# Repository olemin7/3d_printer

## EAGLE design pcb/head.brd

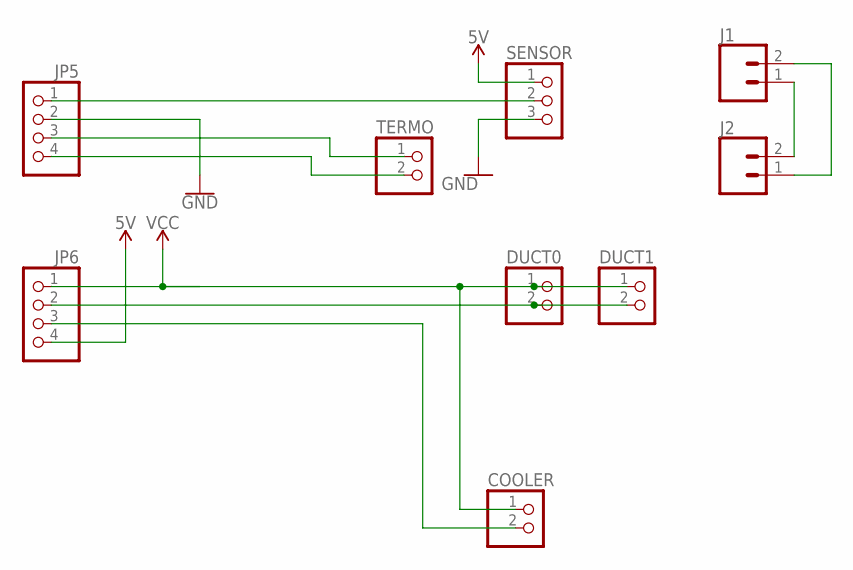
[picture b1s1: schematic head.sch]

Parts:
COOLER: PINHD-1X2; 1X02
DUCT0, DUCT1: PINHD-1X2; 1X02
J1, J2: CONN_025MM; SCREWTERMINAL-5MM-2
JP5, JP6: PINHD-1X4; 1X04
SENSOR: PINHD-1X3; 1X03
TERMO: PINHD-1X2; 1X02

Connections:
5V: JP6.4, SENSOR.1
GND: JP5.2, SENSOR.3
unnamed: JP5.1, SENSOR.2
unnamed: COOLER.2, JP6.3
unnamed: JP5.3, TERMO.1
unnamed: J1.1, J2.2
unnamed: JP5.4, TERMO.2
unnamed: J1.2, J2.1
unnamed: DUCT0.2, DUCT1.2, JP6.2
VCC: COOLER.1, DUCT0.1, DUCT1.1, JP6.1

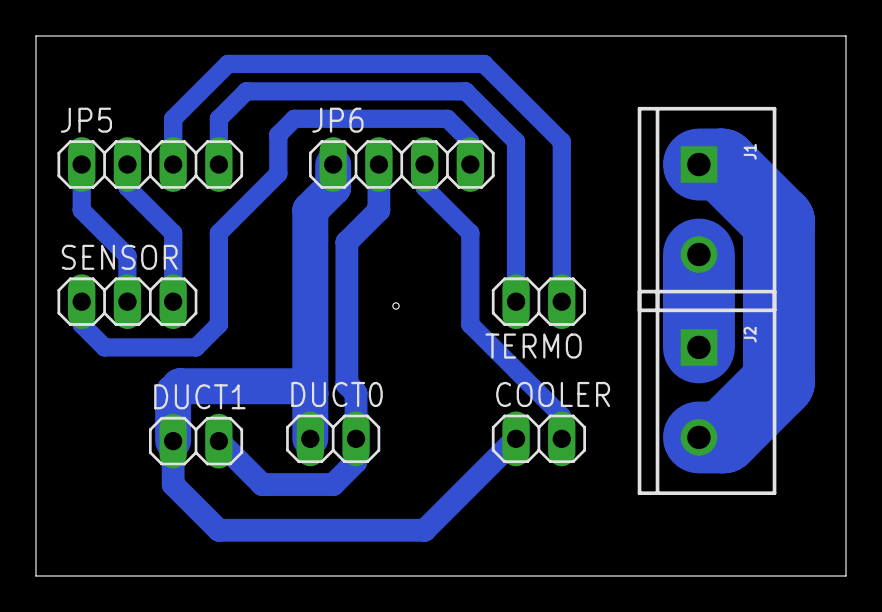
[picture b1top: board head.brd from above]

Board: 2 copper layers, 45.0 x 30.0 mm, 9 parts (0 on the bottom side), 10 nets.

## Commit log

2022-10-28 initial
2022-12-02 setmin temp -15
2022-12-12 xy home to max
2024-02-02 -garbage
2024-02-17 before
2024-03-03 xy mount
2026-04-04 split readmy

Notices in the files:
parts and their libraries:
SparkFun-Connectors: Licensing: Creative Commons ShareAlike 4.0 International - https://creativecommons.org/licenses/by-sa/4.0
